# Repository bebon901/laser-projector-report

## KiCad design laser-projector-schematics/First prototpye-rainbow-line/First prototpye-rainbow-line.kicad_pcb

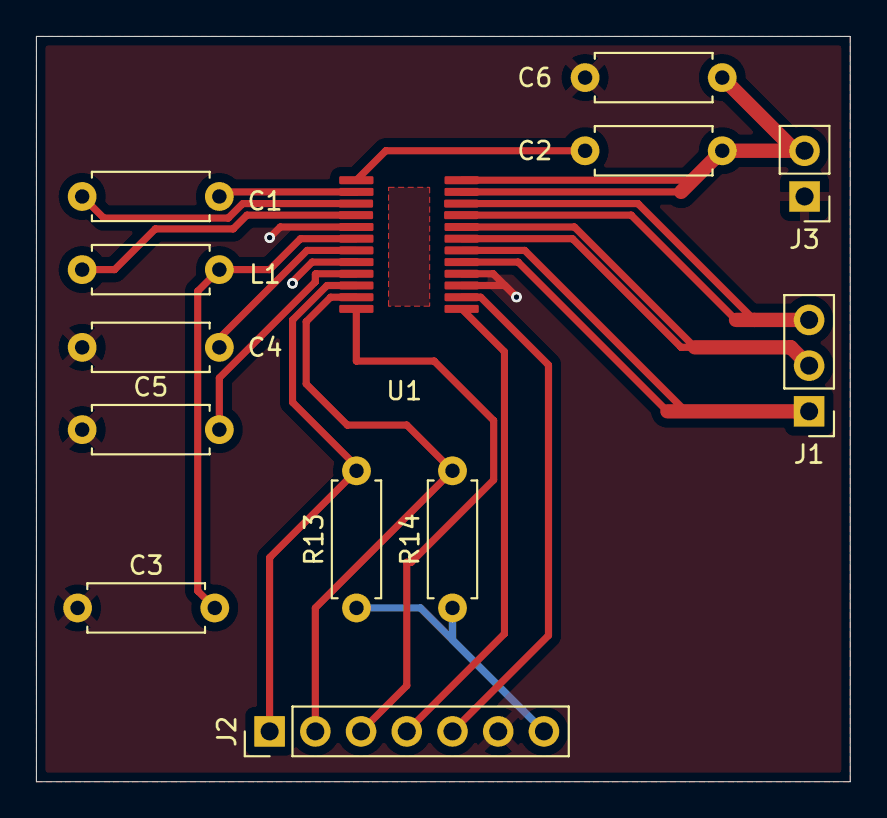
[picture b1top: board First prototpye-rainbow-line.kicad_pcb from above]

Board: 2 copper layers, 45.2 x 41.4 mm, 13 parts (0 on the bottom side), 18 nets.

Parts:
C1, C2: 0.1u; R_Axial_DIN0207_L6.3mm_D2.5mm_P7.62mm_Horizontal
C3, C6: 10u; R_Axial_DIN0207_L6.3mm_D2.5mm_P7.62mm_Horizontal
C4, C5: 1u; R_Axial_DIN0207_L6.3mm_D2.5mm_P7.62mm_Horizontal
J1: Conn_01x03_Pin; PinHeader_1x03_P2.54mm_Vertical
J2: Conn_01x07_Pin; PinHeader_1x07_P2.54mm_Vertical
J3: Conn_01x02_Pin; PinHeader_1x02_P2.54mm_Vertical
L1: 47u; R_Axial_DIN0207_L6.3mm_D2.5mm_P7.62mm_Horizontal
R13, R14: 4.7k; R_Axial_DIN0207_L6.3mm_D2.5mm_P7.62mm_Horizontal
U1: drv10983

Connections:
+3V3: J2.7, R13.1, R14.1
+12V: C2.1, C6.2, J3.2, U1.23 (VCC), U1.24 (VCC)
GND: C3.1, C4.1, C5.1, C6.1, J2.6, J3.1, U1.5 (SWGND), U1.8 (GND), U1.15 (PGND), U1.16 (PGND)
unnamed: J1.1, U1.17 (U), U1.18 (U)
unnamed: J1.2, U1.19 (V), U1.20 (V)
unnamed: J1.3, U1.21 (W), U1.22 (W)
unnamed: J2.1, R13.2, U1.10 (SCL)
unnamed: J2.2, R14.2, U1.11 (SDA)
unnamed: J2.3, U1.12 (FG)
unnamed: J2.4, U1.13 (SPEED)
unnamed: J2.5, U1.14 (DIR)
unnamed: C1.1, U1.3 (CPN)
unnamed: C1.2, U1.2 (CPP)
unnamed: L1.2, U1.4 (SW)
unnamed: C4.2, U1.7 (V1P8)
unnamed: C5.2, U1.9 (V3P3)
unnamed: C2.2, U1.1 (VCP)
unnamed: C3.2, L1.1, U1.6 (VREG)

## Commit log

2026-05-29 Upload files for report
